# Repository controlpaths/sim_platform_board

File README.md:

# Platform Board

This board is intended to run real time simulation models and connect them to different commercial platforms like Arduino or TI Launchpad. The core of the board is an FPGA able to run models with time steps up to 100ns.

The board is based on a 4-layer PCB with an RP2040 as a platform manager. 

## FPGA 

The FPGA used is the AMD Spartan 7 s15 with 15K logic cells. The package used is FTGB196, which makes the board compatible with FPGAs up to 50k logic cells.

## DAC outputs

The board features two Digital to Analog converters with 8 channels each. The output range of the DAC is 0 - 3 volts with 12 bit resolutions, and an update rate up to 100 ksps.

## Control boards

The platform board is compatible with:

- Arduino MKR
- Arduino Portenta
- Raspberry PI Pico
- Texas Instruments Launchpad Boards

## Build your own

The Platform Board is open-source, so you can use the output files to manufacture your own in [JLCPCB](https://jlcpcb.com/?from=controlpath). You just need to compress the `production_files` directory, and upload it to [JLCPCB](https://jlcpcb.com/?from=controlpath). 

Remember to change the Surface Finish to **LeadFree HASL** to make your board ROHS compliant.

In a few days, you will receive your board at home.

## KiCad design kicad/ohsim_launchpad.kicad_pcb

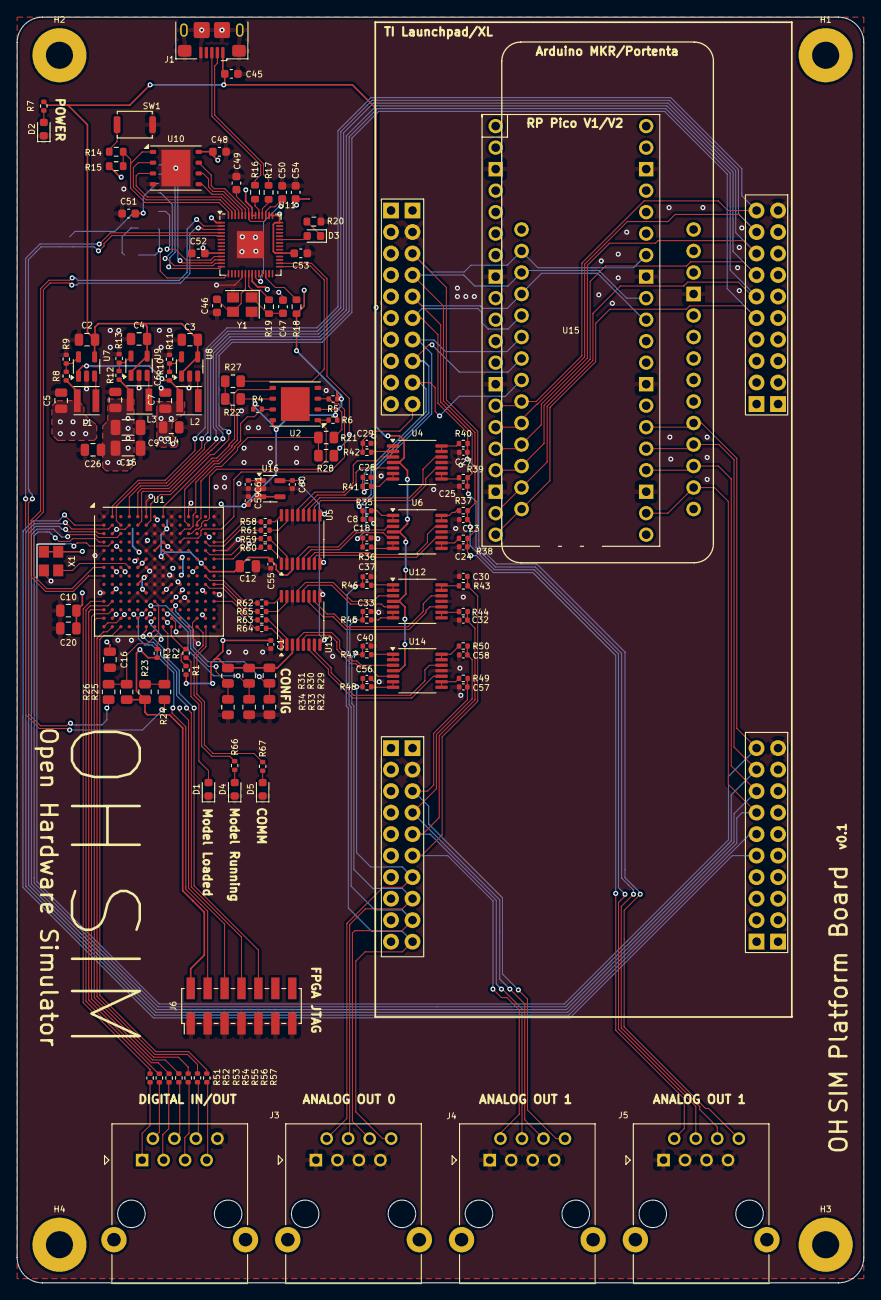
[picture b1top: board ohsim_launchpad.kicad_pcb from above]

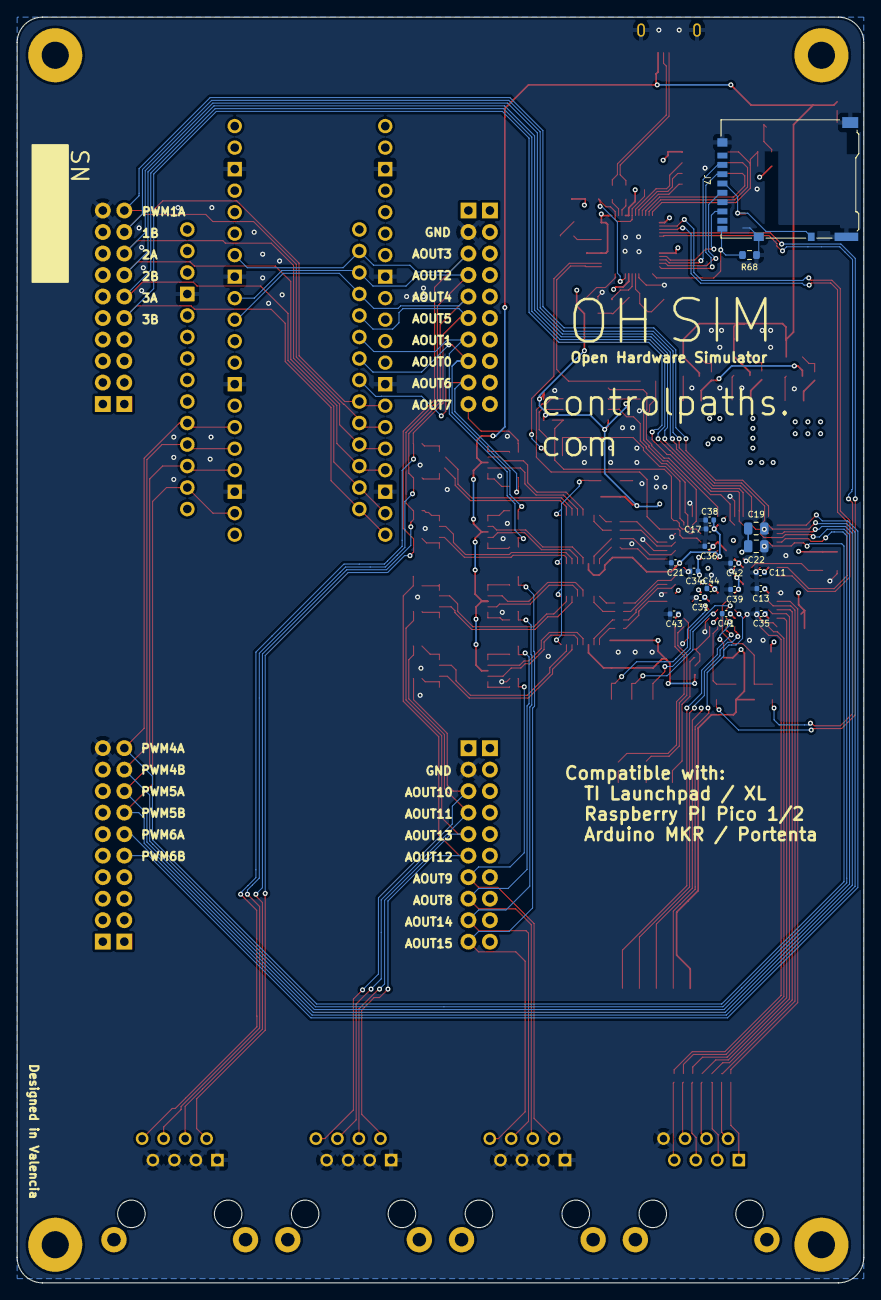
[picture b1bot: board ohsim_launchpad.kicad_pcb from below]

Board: 4 copper layers, 100.0 x 149.5 mm, 168 parts (18 on the bottom side), 158 nets.

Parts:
A1: Arduino_MKR_WiFi_1010_Socket
C1, C11, C13, C17, C21, C31, C34, C35, C36, C38, C39, C41, C42, C43, C44, C55, C59: 0.47u; C_0402_1005Metric
C2, C3, C4, C10, C12, C14, C16, C19, C20, C22, C26: 4u7; C_0805_2012Metric
C5, C6, C7: 10u; C_0805_2012Metric
C8, C18, C23, C24, C25, C27, C28, C29, C30, C32, C33, C37, C40, C56, C57, C58: 1n5; C_0402_1005Metric
C9, C15: 100u; C_1206_3216Metric
C45, C49, C51: 1u; C_0603_1608Metric
C46, C47: 15p; C_0603_1608Metric
C48, C50, C52, C53, C54: 100n; C_0603_1608Metric
C60, C61: 100n; C_0402_1005Metric
D1, D4, D5: DONE; LED_0603_1608Metric
D2: VCC; LED_0603_1608Metric
D3: LED; LED_0603_1608Metric
H1, H2, H3, H4: MountingHole_Pad; MountingHole_3.2mm_M3_Pad
J1: USB_B_Micro; USB_Micro-B_Amphenol_10118193-0001LF_Horizontal
J2, J3, J4, J5: RJ45; RJ45_Ninigi_GE
J6: Conn_02x07_Odd_Even; PinHeader_2x07_P2.00mm_Vertical_SMD
J7: Micro_SD_Card_Det_Hirose_DM3AT; microSD_HC_Hirose_DM3AT-SF-PEJM5
L1, L2, L3: 2u2; IND_LQH3NPN2R2MMEL
R1: 330; R_0402_1005Metric
R2, R51, R52, R53, R54, R55, R56, R57: 100; R_0402_1005Metric
R3, R4, R5, R6, R66, R67: 4k7; R_0402_1005Metric
R7: 10k; R_0402_1005Metric
R8: 100k; R_0402_1005Metric
R9, R12: 22k; R_0402_1005Metric
R10: 240k; R_0402_1005Metric
R11: 120k; R_0402_1005Metric
R13: 33k; R_0402_1005Metric
R14, R19: 1k; R_0603_1608Metric
R15, R18: 10k; R_0603_1608Metric
R16, R17: 27; R_0603_1608Metric
R20, R68: 4k7; R_0603_1608Metric
R21, R22, R24, R25, R27, R28: 0; R_0805_2012Metric
R23, R26, R29, R30, R31, R32, R33, R34: 4k7; R_0805_2012Metric
R35, R36, R37, R38, R39, R40, R41, R42, R43, R44, R45, R46, R47, R48, R49, R50: 1k; R_0402_1005Metric
R58, R59, R60, R61, R62, R63, R64, R65: 27; R_0402_1005Metric
SW1: SW_Push; SW_Push_SPST_NO_Alps_SKRK
U1: xc7s25ftgb196; Xilinx_FTGB196
U2: MX25L12833F; WSON-8-1EP_6x5mm_P1.27mm_EP3.4x4mm
U3: LAUNCHXL-F28379D; MOD_LAUNCHXL-F28379D
U4, U6, U12, U14: LMV324; TSSOP-14_4.4x5mm_P0.65mm
U5, U13: AD53x8; TSSOP-16_4.4x5mm_P0.65mm
U7, U8, U9: TLV62565DBVR; SOT-23-5
U10: W25Q32JVZP; WSON-8-1EP_6x5mm_P1.27mm_EP3.4x4.3mm
U11: RP2040; QFN-56-1EP_7x7mm_P0.4mm_EP3.2x3.2mm
U15: Pico; RPi_Pico_SMD_TH
U16: REF2030; SOT-23-5
X1: SG-8018CE; Crystal_SMD_3225-4Pin_3.2x2.5mm
Y1: 12MHz; Crystal_SMD_3225-4Pin_3.2x2.5mm

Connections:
+1V0: C7.1, C9.1, C15.1, C19.1, C22.1, C26.1, C36.1, C39.1, C42.1, C44.1, L3.2, R12.1, U1.D6 (VCCINT[10]), U1.D8 (VCCINT[10]), U1.E5 (VCCBRAM[3]), U1.E7 (VCCINT[10]), U1.E9 (VCCINT[10]), U1.F6 (VCCINT[10]), U1.G5 (VCCBRAM[3]), U1.G9 (VCCINT[10]), U1.H6 (VCCINT[10]), U1.J5 (VCCBRAM[3]), U1.J9 (VCCINT[10]), U1.K6 (VCCINT[10]), U1.K8 (VCCINT[10])
+1V1: C49.2, C50.2, U11.23 (DVDD), U11.45 (VREG_VOUT), U11.50 (DVDD)
+1V8: C6.1, C14.1, C31.1, C34.1, L2.2, R10.1, U1.F10 (VCCAUX[4]), U1.H10 (VCCAUX[4]), U1.K10 (VCCAUX[4]), U1.L9 (VCCAUX[4]), U7.1 (EN)
+3V3: C1.1, C5.1, C10.1, C11.1, C12.1, C13.1, C16.1, C17.1, C20.1, C21.1, C35.1, C38.1, C41.1, C43.1, C48.1, C51.2, C52.2, C53.2, C54.2, C55.1, C59.2, J6.2, J7.4 (VDD), J7.10 (DET_A), L1.2, R1.2, R3.2, R4.1, R5.1, R6.1, R8.1, R15.2, R18.2, R23.2, R26.2, R29.1, R30.1, R31.1, U1.B8 (VCCBATT_0), U1.F8 (VCCADC_0), U1.G2 (VCCO_34[3]), U1.G13 (VCCO_14[3]), U1.K2 (VCCO_34[3]), U1.K13 (VCCO_14[3]), U1.N2 (VCCO_34[3]), U1.N6 (VCCO_0[2]), U1.N8 (VCCO_0[2]), U1.N13 (VCCO_14[3]), U2.8 (VCC), U5.3 (VDD), U10.8 (VCC), U11.1 (IOVDD), U11.10 (IOVDD), U11.22 (IOVDD), U11.33 (IOVDD), U11.42 (IOVDD), U11.43 (ADC_AVDD), U11.44 (VREG_IN), U11.48 (USB_VDD), U11.49 (IOVDD), U13.3 (VDD), U16.3 (EN), U16.4 (IN), X1.1 (OE), X1.4 (Vcc)
+5V: C2.1, C3.1, C4.1, C45.2, J1.1 (VBUS), R7.1, U4.4 (V+), U6.4 (V+), U7.4 (VIN), U8.1 (EN), U8.4 (VIN), U9.1 (EN), U9.4 (VIN), U12.4 (V+), U14.4 (V+)
AOUT0: A1.A5, C8.1, R35.2, U3.J3_8 (ADCINB2/ANALOGIN)
AOUT1: A1.A4, C18.1, R36.2, U3.J3_7 (ADCINC2/ANALOGIN)
AOUT2: A1.A1, C23.1, J5.4, R37.2, U3.J3_4 (ADCINC3/ANALOGIN), U15.32 (GPIO27_ADC1)
AOUT3: A1.A0 (A0/DAC), C24.1, J5.2, R38.2, U3.J3_3 (ADCIN14/ANALOGIN), U15.34 (GPIO28_ADC2)
AOUT4: A1.A2, C25.1, J5.6, R39.2, U3.J3_5 (ADCINB3/ANALOGIN), U15.31 (GPIO26_ADC0)
AOUT5: A1.A3, C27.1, J5.8, R40.2, U3.J3_6 (ADCINA3/ANALOGIN)
AOUT6: A1.A6, C28.1, R41.2, U3.J3_9 (ADCINA2/ANALOGIN)
AOUT7: C29.1, R42.2, U3.J3_10 (ADCINA0/ANALOGIN(DACA))
AOUT8: C40.1, J3.4, R47.2, U3.J7_8 (ADCINB4/ANALOGIN)
AOUT9: C56.1, J3.2, R48.2, U3.J7_7 (ADCINC4/ANALOGIN)
AOUT10: C57.1, J4.8, R49.2, U3.J7_3 (ADCIN15/ANALOGIN)
AOUT11: C58.1, J4.6, R50.2, U3.J7_4 (ADCINC5/ANALOGIN)
AOUT12: C30.1, J4.2, R43.2, U3.J7_6 (ADCINA5/ANALOGIN)
AOUT13: C32.1, J4.4, R44.2, U3.J7_5 (ADCINB5/ANALOGIN)
AOUT14: C33.1, J3.6, R45.2, U3.J7_9 (ADCINA4/ANALOGIN)
AOUT15: C37.1, J3.8, R46.2, U3.J7_10 (ADCINA1/ANALOGIN(DACB))
COMM_LED: R67.2, U1.P13 (IO_L22N_T3_D20_14)
DAC0_DIN: R61.2, U1.D13 (IO_L8N_T1_D12_14)
DAC0_LDAC: R60.2, U1.F14 (IO_L9N_T1_DQS_D13_14)
DAC0_SCLK: R58.2, U1.D14 (IO_L11P_T1_SRCC_14)
DAC0_SYNC: R59.2, U1.E13 (IO_L10N_T1_D15_14)
DAC1_DIN: R65.2, U1.J14 (IO_L18N_T2_D27_14)
DAC1_LDAC: R64.2, U1.L14 (IO_L15N_T2_DQS_DOUT_CSO_B_14)
DAC1_SCLK: R62.2, U1.H13 (IO_L14P_T2_SRCC_14)
DAC1_SYNC: R63.2, U1.J13 (IO_L18P_T2_D28_14)
DIO_0: R51.1, U1.L1 (IO_L18N_T2_34)
DIO_1: R52.1, U1.L2 (IO_L22N_T3_34)
DIO_2: R53.1, U1.M1 (IO_L18P_T2_34)
DIO_3: R54.1, U1.M2 (IO_L19N_T3_VREF_34)
DIO_4: R55.1, U1.N1 (IO_L20N_T3_34)
DIO_5: R56.1, U1.P2 (IO_L20P_T3_34)
DIO_6: R57.1, U1.P3 (IO_L21N_T3_DQS_34)
DONE_RP2040: R1.1, R2.2, U1.P9 (DONE_0)
FLASH_CS: R14.1, R15.1, U10.1 (~CS), U11.56 (QSPI_SS)
FLASH_DIN_RP2040: R28.2, U11.30 (GPIO19)
FLASH_RP2040_SCLK: U10.6 (CLK), U11.52 (QSPI_SCLK)
FLASH_SCLK: R22.2, U2.6 (SCLK)
FLASH_SCLK_RP2040: R27.2, U11.29 (GPIO18)
FLASH_SD0: U10.5 (DI(IO0)), U11.53 (QSPI_SD0)
FLASH_SD1: U10.2 (DO(IO1)), U11.55 (QSPI_SD1)
FLASH_SD2: U10.3 (IO2), U11.54 (QSPI_SD2)
FLASH_SD3: U10.7 (IO3), U11.51 (QSPI_SD3)
FPGA_FLASH_SCLK: R22.1, R27.1, U1.A8 (CCLK_0)
FPGA_M0: R31.2, R34.1, U1.M7 (M0_0)
FPGA_M1: R30.2, R33.1, U1.M8 (M1_0)
FPGA_M2: R29.2, R32.1, U1.M9 (M2_0)
GND: A1.GND, C1.2, C2.2, C3.2, C4.2, C5.2, C6.2, C7.2, C8.2, C9.2, C10.2, C11.2, C12.2, C13.2, C14.2, C15.2, C16.2, C17.2, C18.2, C19.2, C20.2, C21.2, C22.2, C23.2, C24.2, C25.2, C26.2, C27.2, C28.2, C29.2, C30.2, C31.2, C32.2, C33.2, C34.2, C35.2, C36.2, C37.2, C38.2, C39.2, C40.2, C41.2, C42.2, C43.2, C44.2, C45.1, C46.1, C47.1, C48.2, C49.1, C50.1, C51.1, C52.1, C53.1, C54.1, C55.2, C56.2, C57.2, C58.2, C59.1, C60.2, C61.2, D1.1 (K), D2.1 (K), D4.1 (K), D5.1 (K), J1.5 (GND), J1.6 (Shield), J2.8, J3.1, J3.3, J3.5, J3.7, J4.1, J4.3, J4.5, J4.7, J5.1, J5.3, J5.5, J5.7, J6.1, J6.3, J6.5, J6.7, J6.9, J6.11, J6.13, J7.6 (VSS), J7.11 (SHIELD), R9.2, R11.2, R13.2, R20.1, R32.2, R33.2, R34.2, R68.1, SW1.1, U1.A1 (GND[50]), U1.A6 (GND[50]), U1.A9 (GND[50]), U1.A11 (GND[50]), U1.A14 (GND[50]), U1.B4 (GND[50]), U1.B7 (GND[50]), U1.B9 (GND[50]), U1.C2 (GND[50]), U1.C6 (GND[50]), U1.C7 (GND[50]), U1.C8 (GND[50]), U1.C9 (GND[50]), U1.C13 (GND[50]), U1.D5 (GND[50]), U1.D7 (GND[50]), U1.D9 (GND[50]), U1.D11 (GND[50]), U1.E1 (GND[50]), U1.E3 (GND[50]), U1.E6 (GND[50]), U1.E8 (GND[50]), U1.E10 (GND[50]), U1.E14 (GND[50]), U1.F5 (GND[50]), U1.F7 (GNDADC_0), U1.F9 (GND[50]), U1.G3 (GND[50]), U1.G6 (GND[50]), U1.G7 (VREFN_0), U1.G8 (VP_0), U1.G10 (GND[50]), U1.G12 (GND[50]), U1.H5 (GND[50]), U1.H7 (VN_0), U1.H8 (VREFP_0), U1.H9 (GND[50]), U1.J6 (GND[50]), U1.J7 (DXN_0), U1.J8 (DXP_0), U1.J10 (GND[50]), U1.K1 (GND[50]), U1.K5 (GND[50]), U1.K7 (GND[50]), U1.K9 (GND[50]), U1.K14 (GND[50]), U1.L4 (GND[50]), U1.L6 (GND[50]), U1.L8 (GND[50]), U1.L10 (GND[50]), U1.L11 (GND[50]), U1.N3 (GND[50]), U1.N5 (GND[50]), U1.N9 (GND[50]), U1.N12 (GND[50]), U1.P1 (GND[50]), U1.P14 (GND[50]), U2.4 (GND), U3.J2_10 (GND_J2), U3.J3_2 (GND_J3), U3.J6_10 (GND_J6), U3.J7_2 (GND_J7), U4.11 (V-), U5.14 (GND), U6.11 (V-), U7.2 (GND), U8.2 (GND), U9.2 (GND), U10.4 (GND), U10.9 (EP), U11.19 (TESTEN), U11.57 (GND), U12.11 (V-), U13.14 (GND), U14.11 (V-), U15.3 (GND), U15.8 (GND), U15.13 (GND), U15.18 (GND), U15.23 (GND), U15.28 (GND), U15.33 (AGND), U15.38 (GND), U16.2 (GND), X1.2 (GND), Y1.2, Y1.4
INIT_B: R23.1, R24.1, U1.P8 (INIT_B_0)
INIT_B_RP2040: R24.2, U11.4 (GPIO2)
JTAG_TCK: J6.6, U1.A7 (TCK_0)
JTAG_TDI: J6.10, U1.P7 (TDI_0)
JTAG_TDO: J6.8, U1.P6 (TDO_0)
JTAG_TMS: J6.4, U1.M6 (TMS_0)
MODEL_RUNNING: R66.2, U1.P12 (IO_L22P_T3_D21_14)
unnamed: C47.2, R19.1, Y1.1
unnamed: D1.2 (A), R2.1
unnamed: D2.2 (A), R7.2
unnamed: D3.2 (A), U11.37 (GPIO25)
unnamed: D3.1 (K), R20.2
unnamed: D4.2 (A), R66.1
unnamed: D5.2 (A), R67.1
unnamed: J1.3 (D+), R16.1
unnamed: J1.2 (D-), R17.1
unnamed: J2.1, R51.2
unnamed: J2.2, R52.2
unnamed: J2.3, R53.2
unnamed: J2.4, R54.2
unnamed: J2.5, R55.2
unnamed: J2.6, R56.2
unnamed: J2.7, R57.2
unnamed: R14.2, SW1.2
unnamed: R3.1, U1.N7 (CFGBVS_0)
unnamed: R21.1, R28.1, U1.B12 (IO_L1N_T0_D01_DIN_14)
unnamed: U1.B11 (IO_L1P_T0_D00_MOSI_14), U2.5 (SI/SIO0)
unnamed: R4.2, U1.C10 (IO_L2N_T0_D03_14), U2.7 (~RESET/SIO3)
unnamed: R5.2, U1.D10 (IO_L2P_T0_D02_14), U2.3 (~WP/SIO2)
unnamed: R6.2, U1.C11 (IO_L6P_T0_FCS_B_14), U2.1 (~CS)
unnamed: U1.G4 (IO_L12P_T1_MRCC_34), X1.3 (OUT)
unnamed: R21.2, U2.2 (SO/SIO1)
unnamed: U4.3 (+), U5.13 (VOUT_H)
unnamed: R42.1, U4.1, U4.2 (-)
unnamed: U4.5 (+), U5.12 (VOUT_G)
unnamed: R41.1, U4.6 (-), U4.7
unnamed: U4.10 (+), U5.10 (VOUT_E)
unnamed: R39.1, U4.8, U4.9 (-)
unnamed: U4.12 (+), U5.11 (VOUT_F)
unnamed: R40.1, U4.13 (-), U4.14
unnamed: R61.1, U5.15 (DIN)
unnamed: R58.1, U5.16 (SCLK)
unnamed: U5.4 (VOUT_A), U6.3 (+)
unnamed: U5.5 (VOUT_B), U6.5 (+)
unnamed: U5.6 (VOUT_C), U6.12 (+)
unnamed: U5.7 (VOUT_D), U6.10 (+)
unnamed: R60.1, U5.1 (~LDAC)
unnamed: R59.1, U5.2 (~SYNC)
unnamed: R35.1, U6.1, U6.2 (-)
unnamed: R36.1, U6.6 (-), U6.7
unnamed: R38.1, U6.8, U6.9 (-)
unnamed: R37.1, U6.13 (-), U6.14
unnamed: R8.2, R9.1, U7.5 (FB)
unnamed: L1.1, U7.3 (SW)
unnamed: R10.2, R11.1, U8.5 (FB)
unnamed: L2.1, U8.3 (SW)
unnamed: R12.2, R13.1, U9.5 (FB)
unnamed: L3.1, U9.3 (SW)
unnamed: R18.1, U11.26 (RUN)
unnamed: R17.2, U11.46 (USB_DM)
unnamed: R16.2, U11.47 (USB_DP)
unnamed: C46.2, U11.20 (XIN), Y1.3
unnamed: R19.2, U11.21 (XOUT)
unnamed: U12.3 (+), U13.13 (VOUT_H)
unnamed: R46.1, U12.1, U12.2 (-)
unnamed: U12.5 (+), U13.12 (VOUT_G)
unnamed: R45.1, U12.6 (-), U12.7
unnamed: U12.10 (+), U13.11 (VOUT_F)
unnamed: R44.1, U12.8, U12.9 (-)
unnamed: U12.12 (+), U13.10 (VOUT_E)
unnamed: R43.1, U12.13 (-), U12.14
unnamed: R65.1, U13.15 (DIN)
unnamed: R62.1, U13.16 (SCLK)
unnamed: U13.4 (VOUT_A), U14.3 (+)
unnamed: U13.5 (VOUT_B), U14.5 (+)
unnamed: U13.6 (VOUT_C), U14.10 (+)
unnamed: U13.7 (VOUT_D), U14.12 (+)
unnamed: R64.1, U13.1 (~LDAC)
unnamed: R63.1, U13.2 (~SYNC)
unnamed: R47.1, U14.1, U14.2 (-)
unnamed: R48.1, U14.6 (-), U14.7
unnamed: R49.1, U14.8, U14.9 (-)
unnamed: R50.1, U14.13 (-), U14.14
unnamed: C61.1, U16.1 (Vbias)
PROGRAM_B: R25.1, R26.1, U1.L7 (PROGRAM_B_0)
PROGRAM_B_RP2040: R25.2, U11.5 (GPIO3)
PWM1A: A1.D0, U1.A2 (IO_L3N_T0_DQS_34), U3.J4_10 (GPIO0/PWMOUT1A), U15.14 (GPIO10)
PWM1B: A1.D1, U1.B3 (IO_L3P_T0_DQS_34), U3.J4_9 (GPIO1/PWMOUT1B), U15.15 (GPIO11)
PWM2A: A1.D2, U1.A4 (IO_L2P_T0_34), U3.J4_8 (GPIO2//PWMOUT2A), U15.16 (GPIO12)
PWM2B: A1.D3, U1.A5 (IO_L4N_T0_34), U3.J4_7 (GPIO3/PWMOUT2B), U15.17 (GPIO13)
PWM3A: A1.D4, U1.B5 (IO_L4P_T0_34), U3.J4_6 (GPIO4/PWMOUT3A), U15.19 (GPIO14)
PWM3B: A1.D5, U1.B6 (IO_0_34), U3.J4_5 (GPIO5/PWMOUT3B), U15.20 (GPIO15)
PWM4A: A1.D10 (D10_MISO), U1.D2 (IO_L10N_T1_34), U3.J8_10 (GPIO6/PWMOUT4A), U15.26 (GPIO20)
PWM4B: A1.D9 (D9_SCK), U1.D1 (IO_L11P_T1_SRCC_34), U3.J8_9 (GPIO7/PWMOUT4B), U15.25 (GPIO19)
PWM5A: A1.D8 (D8_MOSI), U1.C3 (IO_L1N_T0_34), U3.J8_8 (GPIO8/PWMOUT5A), U15.24 (GPIO18)
PWM5B: A1.D7, U1.C1 (IO_L11N_T1_SRCC_34), U3.J8_7 (GPIO9/PWMOUT5B), U15.22 (GPIO17)
PWM6A: U1.B2 (IO_L5P_T0_34), U3.J8_6 (GPIO10/PWMOUT6A)
PWM6B: U1.B1 (IO_L5N_T0_34), U3.J8_5 (GPIO11/PWMOUT6B)
RP2040_UART0_RX: U1.G1 (IO_L9P_T1_DQS_34), U11.3 (GPIO1)
RP2040_UART0_TX: U1.H1 (IO_L14N_T2_SRCC_34), U11.2 (GPIO0)
VREF_DAC: C60.1, U5.8 (VREF_ABCD), U5.9 (VREF_EFGH), U13.8 (VREF_ABCD), U13.9 (VREF_EFGH), U16.5 (Vref)
sdcard_cs: J7.2 (DAT3/CD), U11.12 (GPIO9)
sdcard_detection: J7.9 (DET_B), R68.2, U11.15 (GPIO12)
sdcard_miso: J7.7 (DAT0), U11.11 (GPIO8)
sdcard_mosi: J7.3 (CMD), U11.14 (GPIO11)
sdcard_sclk: J7.5 (CLK), U11.13 (GPIO10)

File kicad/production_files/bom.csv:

Reference,Value,Footprint,Qty,DNP,JLCPCB Part #
"C1,C11,C13,C17,C21,C31,C34,C35,C36,C38,C39,C41,C42,C43,C44,C55,C59",0.47u,Capacitor_SMD:C_0402_1005Metric,17,,C106255
"C2,C3,C4,C10,C12,C14,C16,C19,C20,C22,C26",4u7,Capacitor_SMD:C_0805_2012Metric,11,,C162420
"C5,C6,C7",10u,Capacitor_SMD:C_0805_2012Metric,3,,C105505
"C8,C18,C23,C24,C25,C27,C28,C29,C30,C32,C33,C37,C40,C56,C57,C58",1n5,Capacitor_SMD:C_0402_1005Metric,16,,C106255
"C9,C15",100u,Capacitor_SMD:C_1206_3216Metric,2,,C268006
"C45,C49,C51",1u,Capacitor_SMD:C_0603_1608Metric,3,,
"C46,C47",15p,Capacitor_SMD:C_0603_1608Metric,2,,
"C48,C50,C52,C53,C54",100n,Capacitor_SMD:C_0603_1608Metric,5,,
"C60,C61",100n,Capacitor_SMD:C_0402_1005Metric,2,,C106255
"D1,D4,D5",DONE,LED_SMD:LED_0603_1608Metric,3,,C89814
D2,VCC,LED_SMD:LED_0603_1608Metric,1,,C601673
D3,LED,LED_SMD:LED_0603_1608Metric,1,,C601673
J1,USB_B_Micro,Connector_USB:USB_Micro-B_Amphenol_10118193-0001LF_Horizontal,1,,C132562
"J2,J3,J4,J5",RJ45,Connector_RJ:RJ45_Ninigi_GE,4,,C386758
J7,Micro_SD_Card_Det_Hirose_DM3AT,Connector_Card:microSD_HC_Hirose_DM3AT-SF-PEJM5,1,,C114218
"L1,L2,L3",2u2,lib:IND_LQH3NPN2R2MMEL,3,,C341775
R1,330,Resistor_SMD:R_0402_1005Metric,1,,C881192
"R2,R51,R52,R53,R54,R55,R56,R57",100,Resistor_SMD:R_0402_1005Metric,8,,
"R3,R4,R5,R6,R66,R67",4k7,Resistor_SMD:R_0402_1005Metric,6,,C3017492
R7,10k,Resistor_SMD:R_0402_1005Metric,1,,C328298
R8,100k,Resistor_SMD:R_0402_1005Metric,1,,C131362
"R9,R12",22k,Resistor_SMD:R_0402_1005Metric,2,,C409681
R10,240k,Resistor_SMD:R_0402_1005Metric,1,,C323663
R11,120k,Resistor_SMD:R_0402_1005Metric,1,,C323683
R13,33k,Resistor_SMD:R_0402_1005Metric,1,,C416388
"R14,R19",1k,Resistor_SMD:R_0603_1608Metric,2,,
"R15,R18",10k,Resistor_SMD:R_0603_1608Metric,2,,
"R16,R17",27,Resistor_SMD:R_0603_1608Metric,2,,
"R20,R68",4k7,Resistor_SMD:R_0603_1608Metric,2,,
"R21,R22",0,Resistor_SMD:R_0805_2012Metric,2,,C3017492
"R23,R26,R31,R32,R33",4k7,Resistor_SMD:R_0805_2012Metric,5,,
"R35,R36,R37,R38,R39,R40,R41,R42,R43,R44,R45,R46,R47,R48,R49,R50",1k,Resistor_SMD:R_0402_1005Metric,16,,C409681
"R58,R59,R60,R61,R62,R63,R64,R65",27,Resistor_SMD:R_0402_1005Metric,8,,
SW1,SW_Push,Button_Switch_SMD:SW_Push_SPST_NO_Alps_SKRK,1,,C115357
U1,xc7s25ftgb196,Package_BGA:Xilinx_FTGB196,1,,C1521659
U2,MX25L12833F,Package_SON:WSON-8-1EP_6x5mm_P1.27mm_EP3.4x4mm,1,,C2802978
"U4,U6,U12,U14",LMV324,Package_SO:TSSOP-14_4.4x5mm_P0.65mm,4,,
"U5,U13",AD53x8,Package_SO:TSSOP-16_4.4x5mm_P0.65mm,2,,C578186
"U7,U8,U9",TLV62565DBVR,Package_TO_SOT_SMD:SOT-23-5,3,,
U10,W25Q32JVZP,Package_SON:WSON-8-1EP_6x5mm_P1.27mm_EP3.4x4.3mm,1,,C2940197
U11,RP2040,Package_DFN_QFN:QFN-56-1EP_7x7mm_P0.4mm_EP3.2x3.2mm,1,,
U16,REF2030,Package_TO_SOT_SMD:SOT-23-5,1,,C528704
X1,SG-8018CE,Crystal:Crystal_SMD_3225-4Pin_3.2x2.5mm,1,,C390488
Y1,12MHz,Crystal:Crystal_SMD_3225-4Pin_3.2x2.5mm,1,,C524716

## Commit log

2024-11-24 upload files
2024-11-24 fix typos
